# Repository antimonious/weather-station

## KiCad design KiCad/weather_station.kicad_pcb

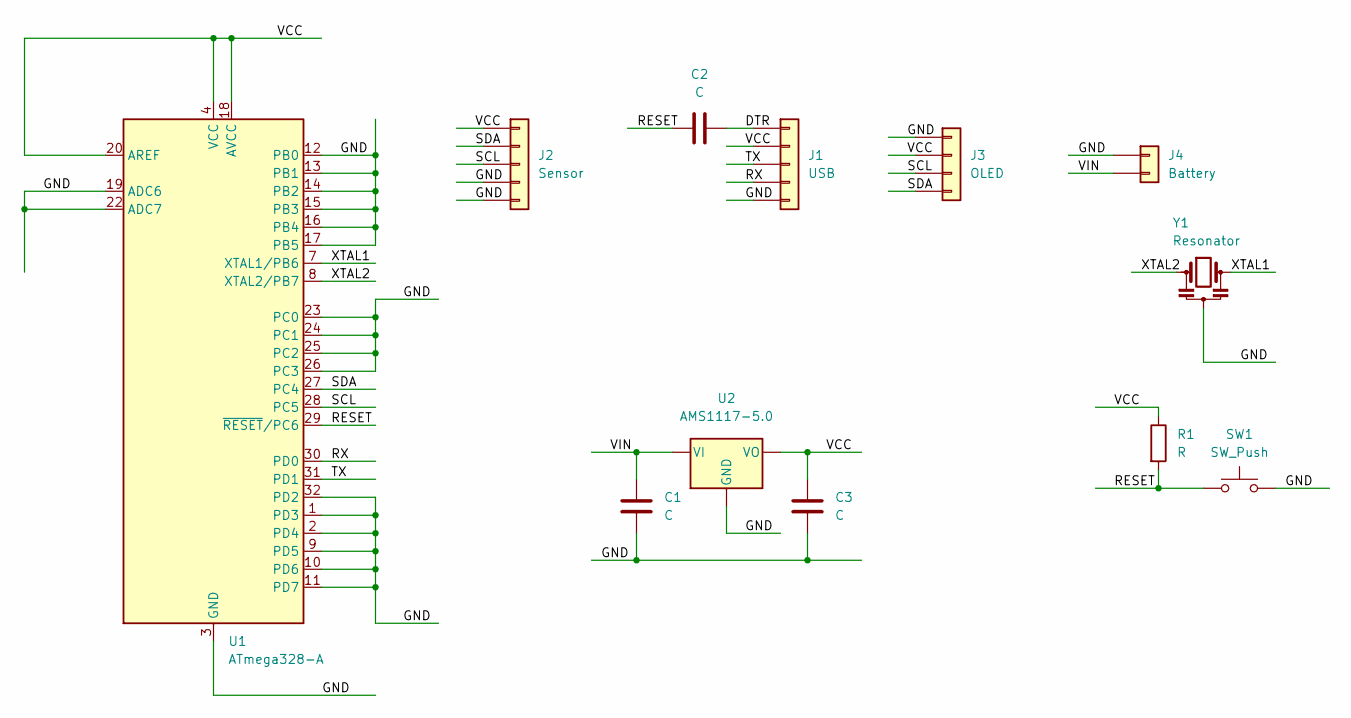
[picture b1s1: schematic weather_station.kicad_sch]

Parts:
C1, C2, C3: C; C_0805_2012Metric
J1: USB; PinHeader_1x05_P2.54mm_Vertical
J2: Sensor; PinHeader_1x05_P2.54mm_Vertical
J3: OLED; PinHeader_1x04_P2.54mm_Vertical
J4: Battery; PinHeader_1x02_P2.54mm_Vertical
R1: R; R_0805_2012Metric
SW1: SW_Push; SW_SPST_CK_RS282G05A3
U1: ATmega328-A; TQFP-32_7x7mm_P0.8mm
U2: AMS1117-5.0; SOT-223-3_TabPin2
Y1: Resonator; Resonator_SMD_Murata_CSTxExxV-3Pin_3.0x1.1mm

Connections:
/DTR: C2.1, J1.1
/GND: C1.1, C3.1, J1.5, J2.4, J2.5, J3.1, J4.1, SW1.2, U1.1 (PD3), U1.2 (PD4), U1.3 (GND), U1.5 (GND), U1.9 (PD5), U1.10 (PD6), U1.11 (PD7), U1.12 (PB0), U1.13 (PB1), U1.14 (PB2), U1.15 (PB3), U1.16 (PB4), U1.17 (PB5), U1.19 (ADC6), U1.21 (GND), U1.22 (ADC7), U1.23 (PC0), U1.24 (PC1), U1.25 (PC2), U1.26 (PC3), U1.32 (PD2), U2.1 (GND), Y1.2
/RESET: C2.2, R1.2, SW1.1, U1.29 (~RESET/PC6)
/RX: J1.4, U1.30 (PD0)
/SCL: J2.3, J3.3, U1.28 (PC5)
/SDA: J2.2, J3.4, U1.27 (PC4)
/TX: J1.3, U1.31 (PD1)
/VCC: C3.2, J1.2, J2.1, J3.2, R1.1, U1.4 (VCC), U1.6 (VCC), U1.18 (AVCC), U1.20 (AREF), U2.2 (VO)
/VIN: C1.2, J4.2, U2.3 (VI)
/XTAL1: U1.7 (XTAL1/PB6), Y1.3
/XTAL2: U1.8 (XTAL2/PB7), Y1.1

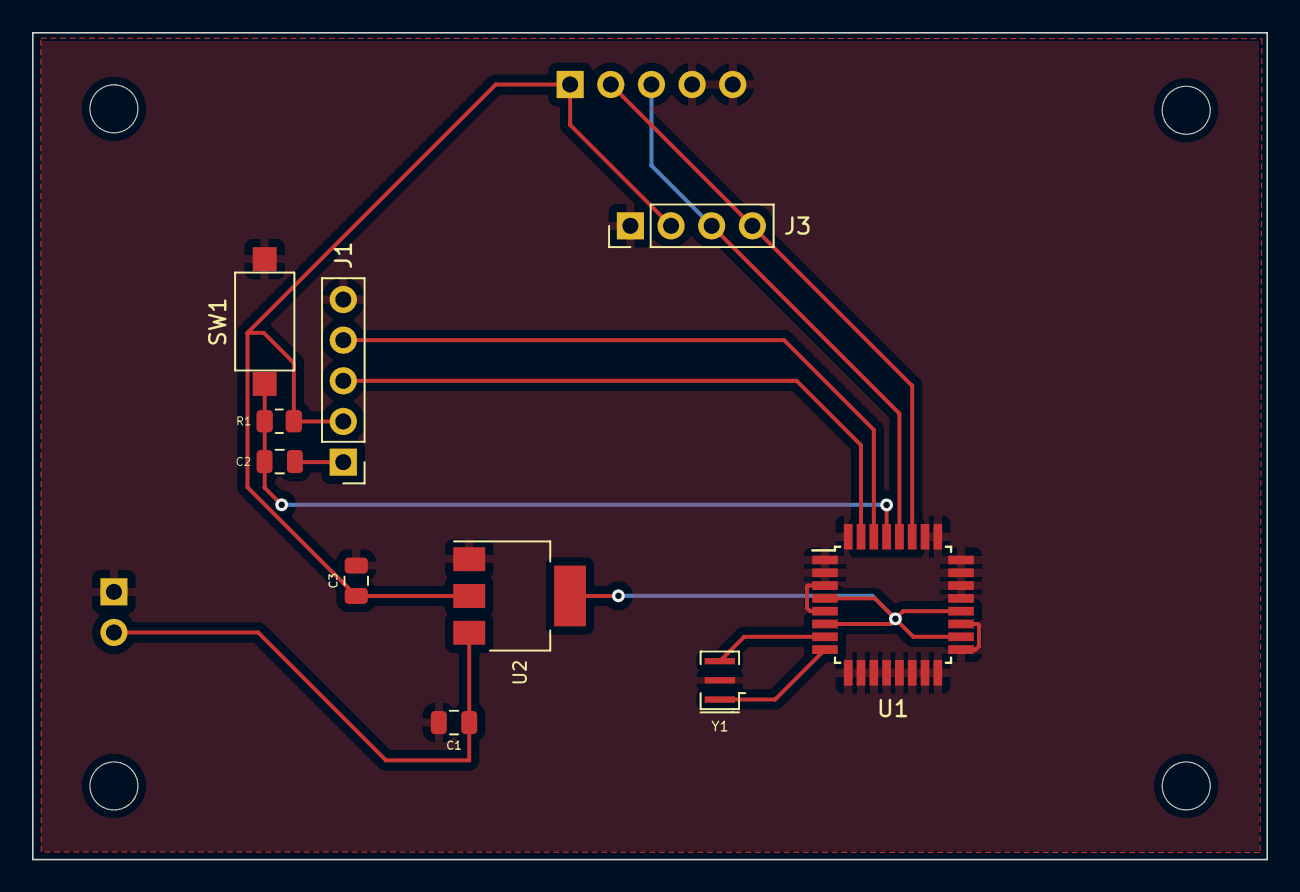
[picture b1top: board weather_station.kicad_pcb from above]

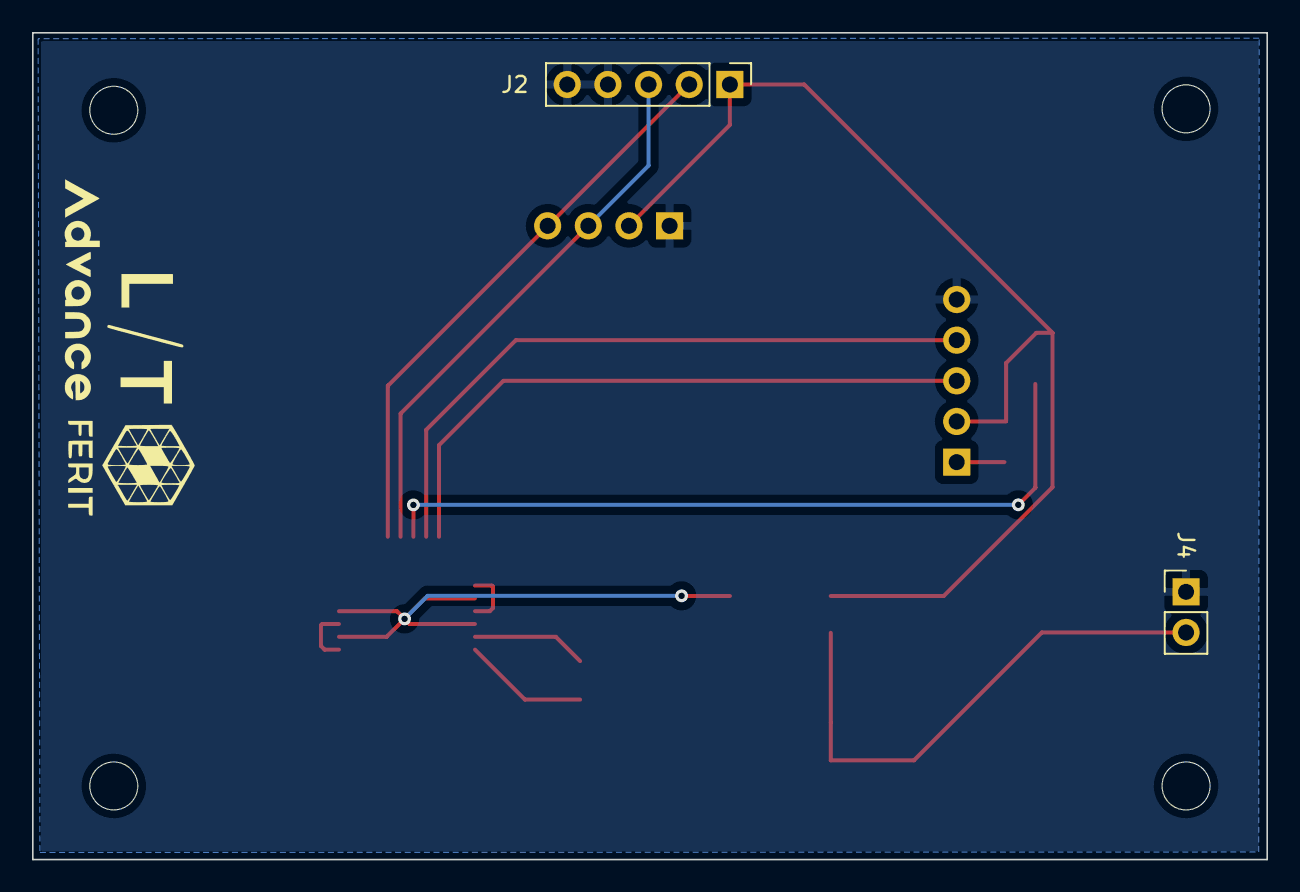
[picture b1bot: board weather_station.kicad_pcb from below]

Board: 2 copper layers, 77.1 x 51.7 mm, 12 parts (2 on the bottom side), 11 nets.

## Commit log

2022-12-21 Create KiCad folder
